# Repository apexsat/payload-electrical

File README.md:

# payload-electrical
PCBs for payload 

## Directory

0_PAY_3D_Model_Library, 0_PAY_Footprint_Library.pretty, 0_PAY_Symbol_Library are libraries for all payload PCBs to use. Use the convention ${KIPRJMOD}/../0_PAY_Symbol_Library/(symbol file) so that library paths are referenced relative to the project path rather than absolute to your specific computer's filesystem.

All PIB and related designs to actually be mounted on satellite should be created as projects in the repo base directory. Any test articles should be created in the test-articles folder. 

simulation should include any relevant MATLAB simulation or spreadsheeting.

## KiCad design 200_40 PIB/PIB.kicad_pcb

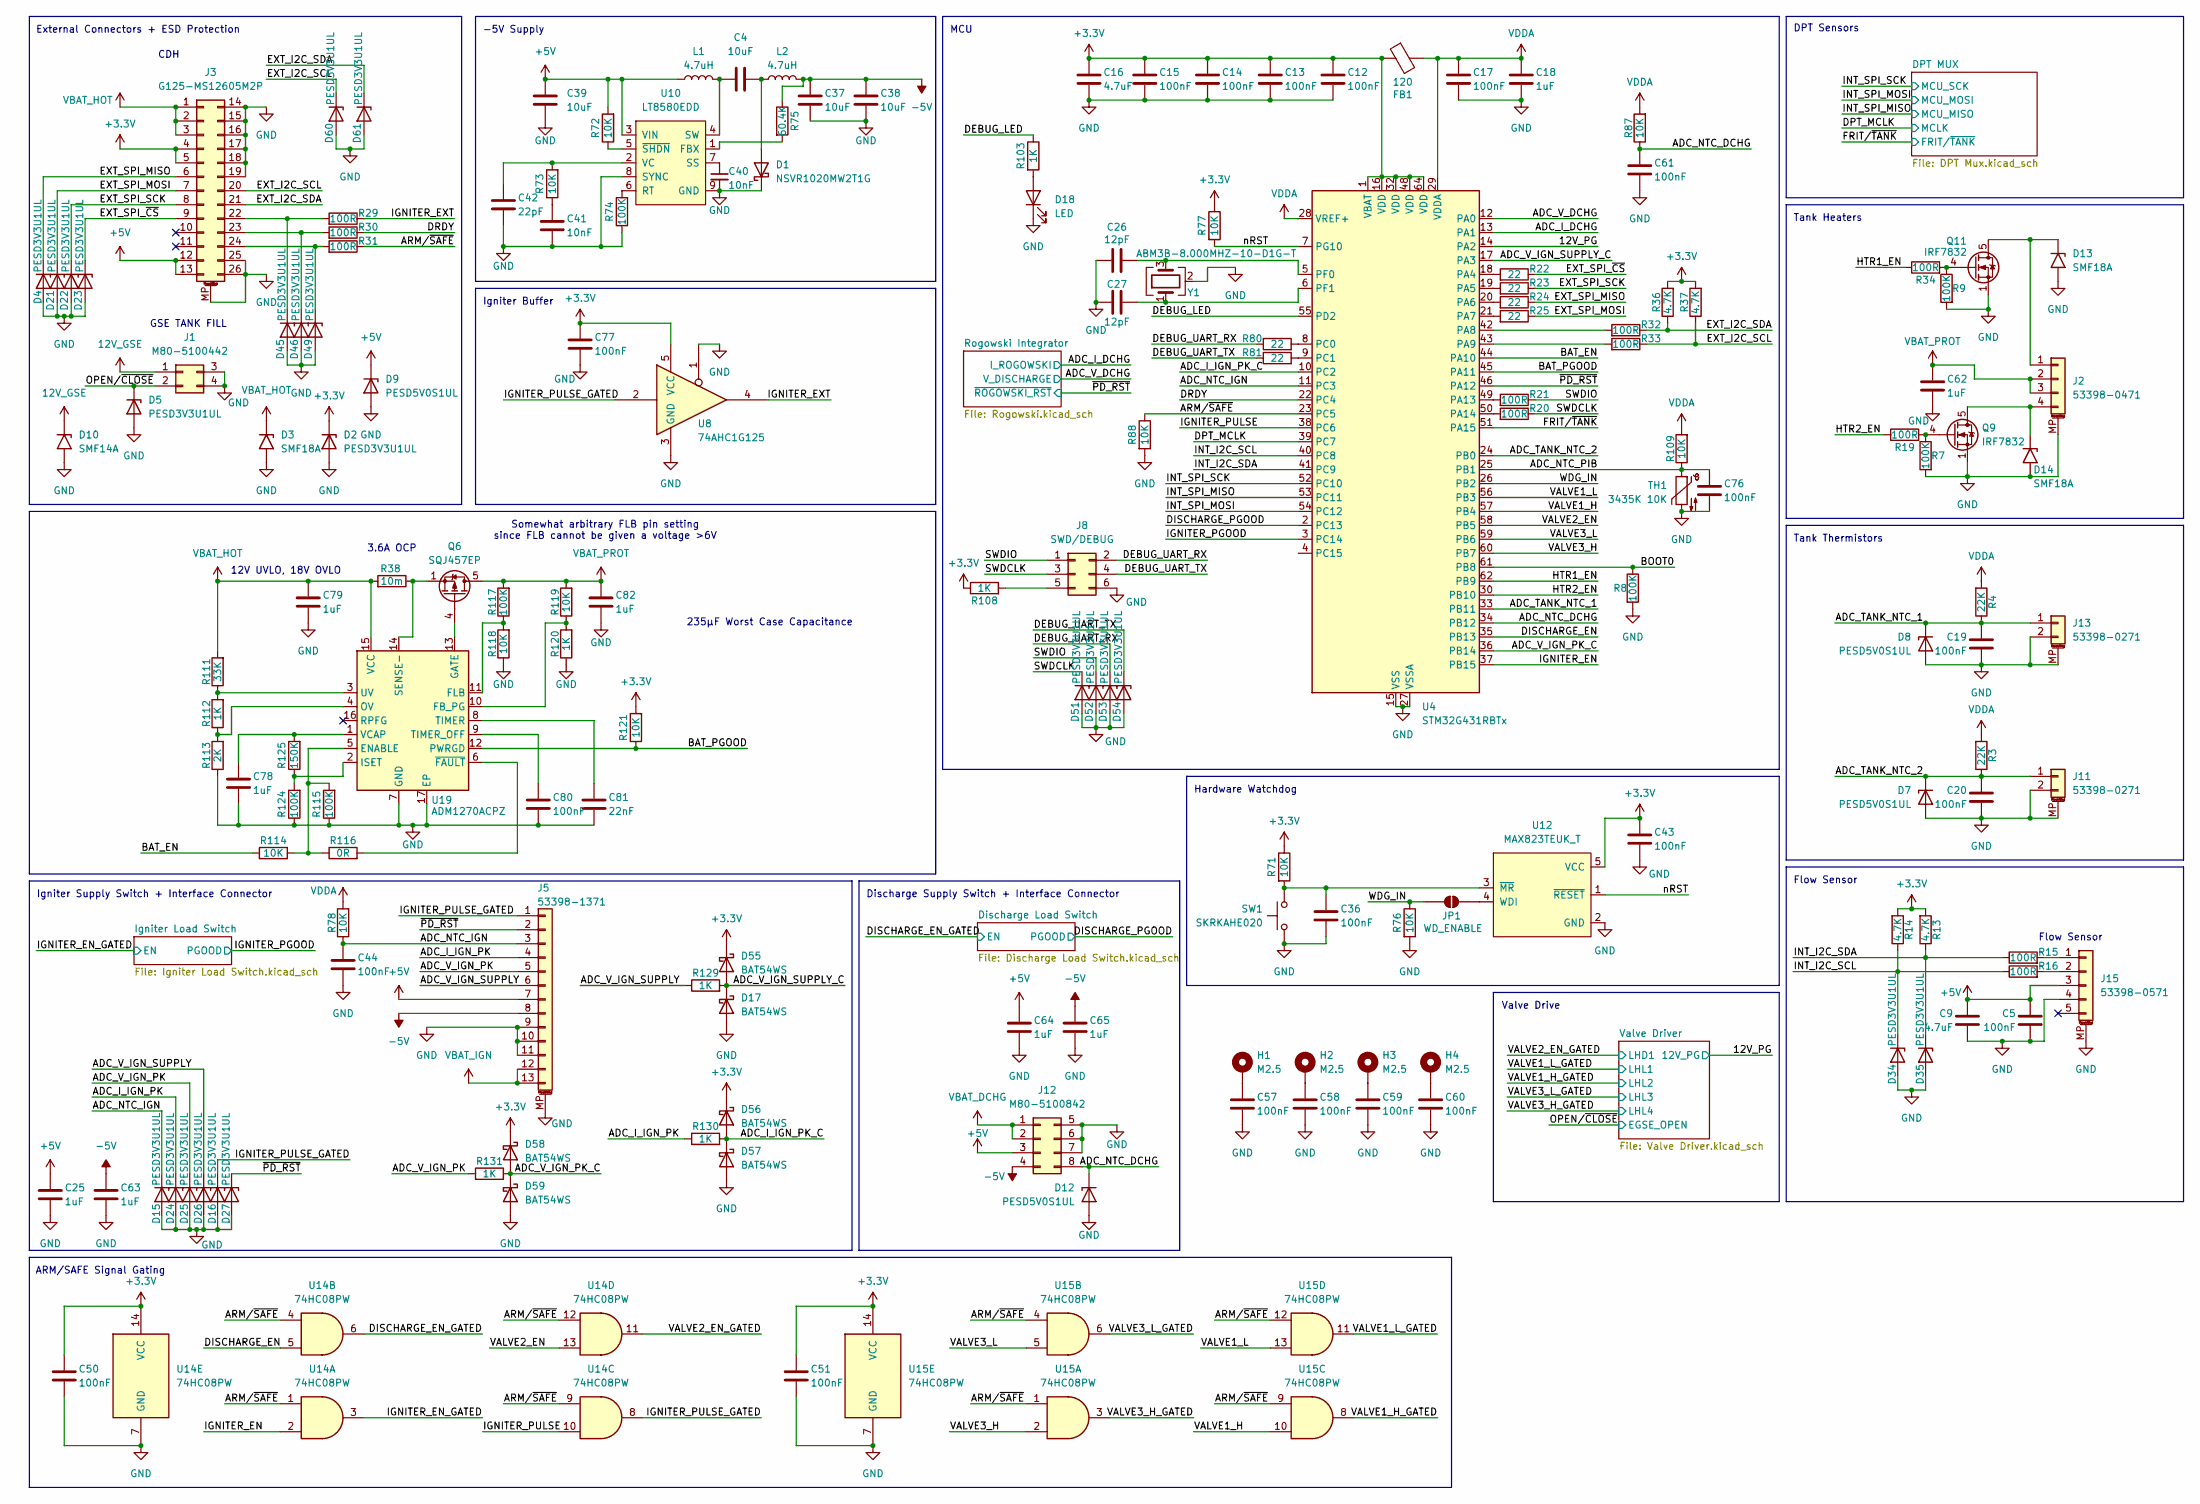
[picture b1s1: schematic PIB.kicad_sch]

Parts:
C4, C37, C38, C39: 10uF; C_0805_2012Metric; Digikey PN 4713-GMC21X7R106K25NTCT-ND
C5, C12, C13, C14, C15, C17, C19, C20, C36, C43, C44, C50, C51, C61, C76, C77, C80: 100nF; C_0402_1005Metric; Digikey PN 490-10672-1-ND
C9, C16: 4.7uF; C_0603_1608Metric; Digikey PN 4713-GMC10X7R475K16NTCT-ND
C18, C25, C62, C63, C64, C65, C78, C79, C82: 1uF; C_0603_1608Metric; Digikey PN 587-3352-1-ND
C26, C27: 12pF; C_0402_1005Metric; Digikey PN 490-16460-1-ND
C40, C41: 10nF; C_0402_1005Metric; Digikey PN 490-4516-1-ND
C42: 22pF; C_0402_1005Metric; Digikey PN 490-16451-1-ND
C57, C58, C59, C60: 100nF; C_0603_1608Metric; Digikey PN 399-C0603C104M5RACTUCT-ND
C81: 22nF; C_0402_1005Metric; Digikey PN 490-4763-1-ND
D1: NSVR1020MW2T1G; D_SOD-323; Digikey PN NSVR1020MW2T1GOSCT-ND
D2, D4, D5, D15, D16, D21, D22, D23, D24, D25, D26, D27, D34, D35, D45, D46, D49, D51, D52, D53, D54, D60, D61: PESD3V3U1UL; D_SOD-882; Digikey PN 1727-4154-1-ND
D3, D13, D14: SMF18A; D_SMF; Digikey PN F5820CT-ND
D7, D8, D9, D12: PESD5V0S1UL; D_SOD-882; Digikey PN 1727-PESD5V0S1ULSYLCT-ND
D10: SMF14A; D_SMF; Digikey PN F5816CT-ND
D17, D55, D56, D57, D58, D59: BAT54WS; D_SOD-323F; Digikey PN 4878-BAT54WSCT-ND
D18: LED; LED_0603_1608Metric; Digikey PN 732-4971-1-ND
FB1: 120; R_0603_1608Metric; Digikey PN 553-2387-1-ND
H1, H2, H3, H4: M2.5; MountingHole_2.7mm_M2.5_DIN965_Pad
J1: M80-5100442; HARWIN_M80-5100442; Digikey PN 952-2343-ND
J2: 53398-0471; Molex_PicoBlade_53398-0471_1x04-1MP_P1.25mm_Vertical; Digikey PN WM7608CT-ND
J3: G125-MS12605M2P; Harwin_Gecko_G125-MS12605M2P_2x13_P1.25mm_Vertical; Digikey PN 952-3677-ND
J5: 53398-1371; Molex_PicoBlade_53398-1371_1x13-1MP_P1.25mm_Vertical; Digikey PN WM7617CT-ND
J8: SWD/DEBUG; PinHeader_2x03_P2.54mm_Vertical_SMD; Digikey PN 952-2121-ND
J11, J13: 53398-0271; Molex_PicoBlade_53398-0271_1x02-1MP_P1.25mm_Vertical; Digikey PN WM7606CT-ND
J12: M80-5100842; HARWIN_M80-5100842; Digikey PN 952-2341-ND
J15: 53398-0571; Molex_PicoBlade_53398-0571_1x05-1MP_P1.25mm_Vertical; Digikey PN WM7609CT-ND
JP1: WD_ENABLE; SolderJumper-2_P1.3mm_Open_Pad1.0x1.5mm
L1, L2: 4.7uH; L_Vishay_IHLP-1616; Digikey PN 541-1051-1-ND
Q6: SQJ457EP; PowerPAK_SO-8_Single; Digikey PN SQJ457EP-T1_GE3CT-ND
Q9, Q11: IRF7832; SOIC-8_3.9x4.9mm_P1.27mm; Digikey PN IRF7832PBFCT-ND
R3, R4: 22K; R_0402_1005Metric; Tolerance 0.1%, 25ppm/C; Digikey PN YAG4210CT-ND
R7, R8, R9, R74, R115, R124: 100K; R_0402_1005Metric; Digikey PN YAG1343CT-ND
R13, R14, R36, R37: 4.7K; R_0402_1005Metric; Digikey PN 311-4.7KLRCT-ND
R15, R16, R19, R20, R21, R29, R30, R31, R32, R33, R34: 100R; R_0402_1005Metric; Digikey PN YAG2301CT-ND
R22, R23, R24, R25, R80, R81: 22; R_0402_1005Metric; Digikey PN 311-22.0LRCT-ND
R38: 10m; R_0805_2012Metric; Digikey PN 273-MCS1320R010FERCT-ND
R71, R72, R73, R76, R77, R88, R114, R121: 10K; R_0402_1005Metric; Digikey PN YAG1346CT-ND
R75: 60.4K; R_0402_1005Metric; Digikey PN YAG1461CT-ND
R78, R87, R109, R118, R119: 10K; R_0402_1005Metric; Tolerance 0.1%, 25ppm/C; Digikey PN YAG1346CT-ND
R103, R108, R129, R130, R131: 1K; R_0402_1005Metric; Digikey PN 13-RT0402BRD131KLCT-ND
R111: 33K; R_0402_1005Metric; Tolerance 0.1%, 25ppm/C; Digikey PN YAG1412CT-ND
R112, R120: 1K; R_0402_1005Metric; Tolerance 0.1%, 25ppm/C; Digikey PN 13-RT0402BRD131KLCT-ND
R113: 2K; R_0402_1005Metric; Tolerance 0.1%, 25ppm/C; Digikey PN YAG2303CT-ND
R116: 0R; R_0402_1005Metric; Digikey PN 311-0.0LRCT-ND
R117: 100K; R_0402_1005Metric; Tolerance 0.1%, 25ppm/C; Digikey PN YAG1343CT-ND
R125: 150K; R_0402_1005Metric; Digikey PN 13-RT0402BRD07150KLCT-ND
SW1: SKRKAHE020; SW_Push_SPST_NO_Alps_SKRK; Digikey PN 4809-SKRKAHE020CT-ND
TH1: 3435K 10K; R_0603_1608Metric; Digikey PN P12011CT-ND
U4: STM32G431RBTx; LQFP-64_10x10mm_P0.5mm; Digikey PN 497-19471-ND
U8: 74AHC1G125; SOT-23-5; Digikey PN 296-8744-1-ND
U10: LT8580EDD; DFN-8_DD; Digikey PN 161-LT8580EDD#TRPBFCT-ND
U12: MAX823TEUK_T; SOT95P280X145-5N; Digikey PN MAX823TEUK+TCT-ND
U14, U15: 74HC08PW; TSSOP-14_4.4x5mm_P0.65mm; Digikey PN 296-26459-5-ND
U19: ADM1270ACPZ; LFCSP-16-1EP_3x3mm_P0.5mm_EP1.5x1.5mm; Digikey PN ADM1270ACPZ-R7CT-ND
Y1: ABM3B-8.000MHZ-10-D1G-T; Crystal_SMD_Abracon_ABM3B-4Pin_5.0x3.2mm; Digikey PN 535-ABM3B-8.000MHZ-10-D1G-TCT-ND

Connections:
12V_GSE: D10.1 (A1), J1.1; also elsewhere on the board
+3.3V: C12.1, C13.1, C14.1, C15.1, C16.1, C43.1, C50.1, C51.1, C77.1, D2.1 (K), D55.1 (K), D56.1 (K), D58.1 (K), FB1.1, J3.4, J3.5, R13.2, R14.2, R36.2, R37.2, R71.1, R77.1, R108.1, R121.2, U4.1 (VBAT), U4.16 (VDD), U4.32 (VDD), U4.48 (VDD), U4.64 (VDD), U8.5 (VCC), U12.5 (VCC), U14.14 (VCC), U15.14 (VCC); also elsewhere on the board
+5V: C5.1, C9.1, C25.1, C39.2, C64.1, D9.1 (K), J3.12, J3.13, J5.7, J12.3, J15.3, L1.1, R72.2, U10.3 (VIN); also elsewhere on the board
-5V: C37.2, C38.2, C63.1, C65.1, J5.8, J12.4, L2.2, R75.1; also elsewhere on the board
/12V_PG: U4.14 (PA2); also elsewhere on the board
/ADC_I_DCHG: U4.13 (PA1); also elsewhere on the board
/ADC_I_IGN_PK: D24.1 (K), J5.4, R130.1
/ADC_I_IGN_PK_C: D56.2 (A), D57.1 (K), R130.2, U4.10 (PC2)
/ADC_NTC_DCHG: C61.1, D12.1 (K), J12.8, R87.1, U4.34 (PB12)
/ADC_NTC_IGN: C44.1, D15.1 (K), J5.3, R78.1, U4.11 (PC3)
/ADC_NTC_PIB: C76.1, R109.1, TH1.1, U4.25 (PB1)
/ADC_TANK_NTC_1: C19.1, D8.1 (K), J13.1, R4.1, U4.33 (PB11)
/ADC_TANK_NTC_2: C20.1, D7.1 (K), J11.1, R3.1, U4.24 (PB0)
/ADC_V_DCHG: U4.12 (PA0); also elsewhere on the board
/ADC_V_IGN_PK: D25.1 (K), J5.5, R131.1
/ADC_V_IGN_PK_C: D58.2 (A), D59.1 (K), R131.2, U4.36 (PB14)
/ADC_V_IGN_SUPPLY: D26.1 (K), J5.6, R129.1
/ADC_V_IGN_SUPPLY_C: D17.1 (K), D55.2 (A), R129.2, U4.17 (PA3)
/ARM/~SAFE: R31.1, R88.1, U4.23 (PC5), U14.1, U14.4, U14.9, U14.12, U15.1, U15.4, U15.9, U15.12
/BAT_EN: R114.1, U4.44 (PA10)
/BAT_PGOOD: R121.1, U4.45 (PA11), U19.12 (PWRGD)
/BOOT0: R8.1, U4.61 (PB8)
/DEBUG_LED: R103.1, U4.55 (PD2)
/DEBUG_UART_RX: D53.1 (K), J8.2, R80.1
/DEBUG_UART_TX: D54.1 (K), J8.4, R81.1
/DISCHARGE_EN: U4.35 (PB13), U14.5
/DISCHARGE_EN_GATED: U14.6; also elsewhere on the board
/DISCHARGE_PGOOD: U4.2 (PC13); also elsewhere on the board
/DPT_MCLK: U4.39 (PC7); also elsewhere on the board
/DRDY: R30.1, U4.22 (PC4)
/EXT_I2C_SCL: D60.1 (K), J3.20, R33.1, R37.1
/EXT_I2C_SDA: D61.1 (K), J3.21, R32.1, R36.1
/EXT_SPI_MISO: D4.1 (K), J3.6, R24.1
/EXT_SPI_MOSI: D21.1 (K), J3.7, R25.1
/EXT_SPI_SCK: D22.1 (K), J3.8, R23.1
/EXT_SPI_~CS: D23.1 (K), J3.9, R22.1
/FRIT/~TANK: U4.51 (PA15); also elsewhere on the board
/HTR1_EN: R34.1, U4.62 (PB9)
/HTR2_EN: R19.1, U4.30 (PB10)
/IGNITER_EN: U4.37 (PB15), U14.2
/IGNITER_EN_GATED: U14.3; also elsewhere on the board
/IGNITER_EXT: R29.1, U8.4
/IGNITER_PGOOD: U4.3 (PC14); also elsewhere on the board
/IGNITER_PULSE: U4.38 (PC6), U14.10
/IGNITER_PULSE_GATED: D16.1 (K), J5.1, U8.2, U14.8
/INT_I2C_SCL: D34.1 (K), R14.1, R16.1, U4.40 (PC8)
/INT_I2C_SDA: D35.1 (K), R13.1, R15.1, U4.41 (PC9)
/INT_SPI_MISO: U4.53 (PC11); also elsewhere on the board
/INT_SPI_MOSI: U4.54 (PC12); also elsewhere on the board
/INT_SPI_SCK: U4.52 (PC10); also elsewhere on the board
/OPEN/~CLOSE: D5.1 (K), J1.2; also elsewhere on the board
/SWDCLK: D51.1 (K), J8.3, R20.1
/SWDIO: D52.1 (K), J8.1, R21.1
/VALVE1_H: U4.57 (PB4), U15.10
/VALVE1_H_GATED: U15.8; also elsewhere on the board
/VALVE1_L: U4.56 (PB3), U15.13
/VALVE1_L_GATED: U15.11; also elsewhere on the board
/VALVE2_EN: U4.58 (PB5), U14.13
/VALVE2_EN_GATED: U14.11; also elsewhere on the board
/VALVE3_H: U4.60 (PB7), U15.2
/VALVE3_H_GATED: U15.3; also elsewhere on the board
/VALVE3_L: U4.59 (PB6), U15.5
/VALVE3_L_GATED: U15.6; also elsewhere on the board
/WDG_IN: JP1.1 (A), R76.1, U4.26 (PB2)
/nRST: R77.2, U4.7 (PG10), U12.1 (~RESET)
/~PD_RST: D27.1 (K), J5.2, U4.46 (PA12); also elsewhere on the board
GND: C5.2, C9.2, C12.2, C13.2, C14.2, C15.2, C16.2, C17.2, C18.2, C19.2, C20.2, C25.2, C26.1, C27.1, C36.2, C37.1, C38.1, C39.1, C40.2, C41.2, C42.2, C43.2, C44.2, C50.2, C51.2, C57.2, C58.2, C59.2, C60.2, C61.2, C62.2, C63.2, C64.2, C65.2, C76.2, C77.2, C78.2, C79.2, C80.2, C81.2, C82.2, D1.1 (K), D2.2 (A), D3.2 (A2), D4.2 (A), D5.2 (A), D7.2 (A), D8.2 (A), D9.2 (A), D10.2 (A2), D12.2 (A), D13.2 (A2), D14.2 (A2), D15.2 (A), D16.2 (A), D17.2 (A), D18.1 (K), D21.2 (A), D22.2 (A), D23.2 (A), D24.2 (A), D25.2 (A), D26.2 (A), D27.2 (A), D34.2 (A), D35.2 (A), D45.2 (A), D46.2 (A), D49.2 (A), D51.2 (A), D52.2 (A), D53.2 (A), D54.2 (A), D57.2 (A), D59.2 (A), D60.2 (A), D61.2 (A), J1.3, J1.4, J2.MP (MountPin), J3.14, J3.15, J3.16, J3.17, J3.18, J3.19, J3.25, J3.26, J3.MP (MountPin), J5.9, J5.10, J5.11, J5.MP (MountPin), J8.6, J11.2, J11.MP (MountPin), J12.5, J12.6, J12.7, J13.2, J13.MP (MountPin), J15.4, J15.MP (MountPin), Q9.1 (S), Q9.2 (S), Q9.3 (S), Q11.1 (S), Q11.2 (S), Q11.3 (S), R7.2, R8.2, R9.2, R74.1, R76.2, R88.2, R113.1, R115.1, R118.1, R120.1, R124.1, SW1.2, TH1.2, U4.15 (VSS), U4.27 (VSSA), U4.31 (VSS), U4.47 (VSS), U4.63 (VSS), U8.1, U8.3 (GND), U10.8 (SYNC), U10.9 (GND), U12.2 (GND), U14.7 (GND), U15.7 (GND), U19.7 (GND), U19.17 (EP), Y1.2 (G), Y1.4 (G); also elsewhere on the board
unnamed: C41.1, R73.1
unnamed: C57.1, H1.1 (1_1)
unnamed: C58.1, H2.1 (1_1)
unnamed: C59.1, H3.1 (1_1)
unnamed: C60.1, H4.1 (1_1)
unnamed: C4.2, D1.2 (A), L2.1
unnamed: D13.1 (A1), J2.1, Q11.5 (D), Q11.6 (D), Q11.7 (D), Q11.8 (D)
unnamed: D14.1 (A1), J2.4, Q9.5 (D), Q9.6 (D), Q9.7 (D), Q9.8 (D)
unnamed: D18.2 (A), R103.2
unnamed: D45.1 (K), J3.22, R29.2
unnamed: D46.1 (K), J3.23, R30.2
unnamed: D49.1 (K), J3.24, R31.2
unnamed: J8.5, R108.2
unnamed: J15.1, R15.2
unnamed: J15.2, R16.2
unnamed: JP1.2 (B), U12.4 (WDI)
unnamed: Q6.4 (G), U19.13 (GATE)
unnamed: Q9.4 (G), R7.1, R19.2
unnamed: Q11.4 (G), R9.1, R34.2
unnamed: R22.2, U4.18 (PA4)
unnamed: R23.2, U4.19 (PA5)
unnamed: R24.2, U4.20 (PA6)
unnamed: R25.2, U4.21 (PA7)
unnamed: R32.2, U4.42 (PA8)
unnamed: R33.2, U4.43 (PA9)
unnamed: R21.2, U4.49 (PA13)
unnamed: R20.2, U4.50 (PA14)
unnamed: R80.2, U4.8 (PC0)
unnamed: R81.2, U4.9 (PC1)
unnamed: C26.2, U4.5 (PF0), Y1.3
unnamed: C27.2, U4.6 (PF1), Y1.1
unnamed: R75.2, U10.1 (FBX)
unnamed: R74.2, U10.6 (RT)
unnamed: C40.1, U10.7 (SS)
unnamed: C4.1, L1.2, U10.4 (SW)
unnamed: C42.1, R73.2, U10.2 (VC)
unnamed: R72.1, U10.5 (~SHDN)
unnamed: C36.1, R71.2, SW1.1, U12.3 (~MR)
unnamed: R114.2, R115.2, R116.1, U19.5 (ENABLE)
unnamed: R119.1, R120.2, U19.10 (FB_PG)
unnamed: R117.1, R118.2, U19.11 (FLB)
unnamed: R124.2, R125.1, U19.2 (ISET)
unnamed: R112.1, R113.2, U19.4 (OV)
unnamed: Q6.1 (S), Q6.2 (S), Q6.3 (S), R38.1, U19.14 (SENSE-)
unnamed: C81.1, U19.8 (TIMER)
unnamed: C80.1, U19.9 (TIMER_OFF)
unnamed: R111.1, R112.2, U19.3 (UV)
unnamed: C78.1, R125.2, U19.1 (VCAP)
unnamed: R116.2, U19.6 (~FAULT)
VBAT_DCHG: J12.1, J12.2; also elsewhere on the board
VBAT_HOT: C79.1, D3.1 (A1), J3.1, J3.2, J3.3, R38.2, R111.2, U19.15 (VCC)
VBAT_IGN: J5.12, J5.13; also elsewhere on the board
VBAT_PROT: C62.1, C82.1, J2.2, J2.3, Q6.5 (D), R117.2, R119.2; also elsewhere on the board
VDDA: C17.1, C18.1, FB1.2, R3.2, R4.2, R78.2, R87.2, R109.2, U4.28 (VREF+), U4.29 (VDDA)

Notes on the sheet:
Tank Thermistors
Flow Sensor
External Connectors + ESD Protection
CDH
Igniter Supply Switch + Interface Connector
-5V Supply
Hardware Watchdog
Somewhat arbitrary FLB pin setting since FLB cannot be given a voltage >6V
ARM/SAFE Signal Gating
Valve Drive
MCU
Discharge Supply Switch + Interface Connector
GSE TANK FILL
3.6A OCP
Tank Heaters
12V UVLO, 18V OVLO
235μF Worst Case Capacitance
Igniter Buffer
DPT Sensors

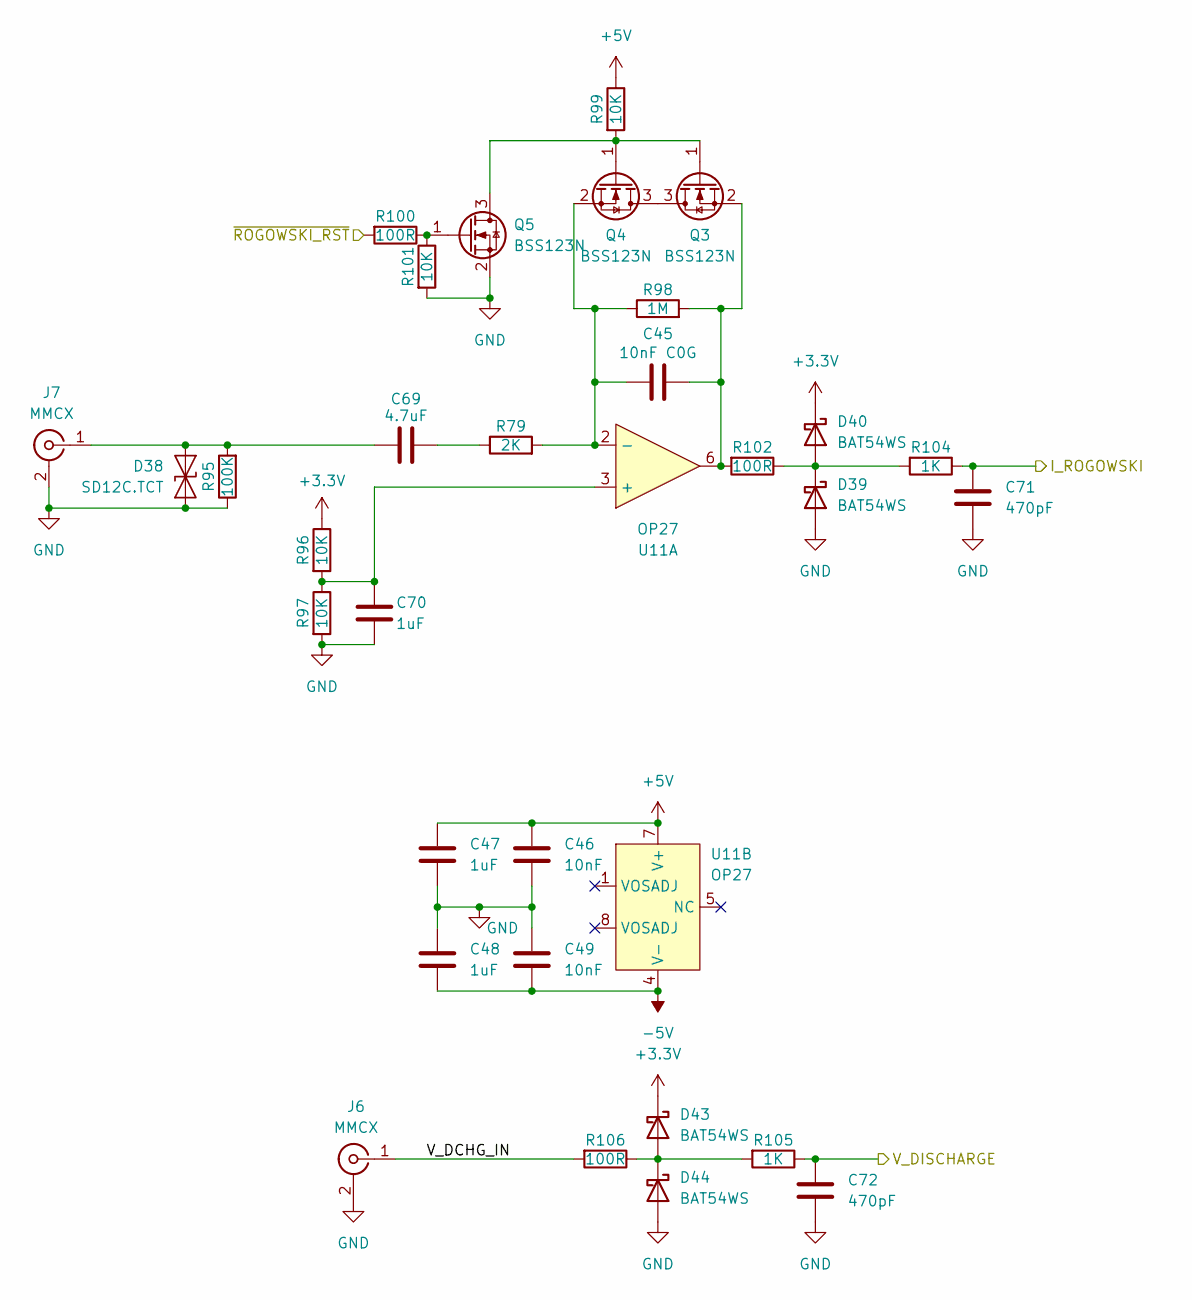
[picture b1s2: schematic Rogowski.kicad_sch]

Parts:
C45: 10nF C0G; C_0603_1608Metric; Digikey PN 490-GRT1885C1E103FA02DCT-ND
C46, C49: 10nF; C_0402_1005Metric; Digikey PN 490-4516-1-ND
C47, C48, C70: 1uF; C_0603_1608Metric; Digikey PN 587-3352-1-ND
C69: 4.7uF; C_0603_1608Metric; Digikey PN 4713-GMC10X7R475K16NTCT-ND
C71, C72: 470pF; C_0402_1005Metric; Digikey PN 490-GCM1555C1H471FA16DCT-ND
D38: SD12C.TCT; D_SOD-323; Digikey PN SD12C.TCTCT-ND
D39, D40, D43, D44: BAT54WS; D_SOD-323F; Digikey PN 4878-BAT54WSCT-ND
J6, J7: MMCX; MMCX_Molex_73415-1471_Vertical; Digikey PN WM5557-ND
Q3, Q4, Q5: BSS123N; SOT-23; Digikey PN BSS123NH6327XTSA1CT-ND
R79: 2K; R_0603_1608Metric; Digikey PN P2.0KDBCT-ND
R95: 100K; R_0603_1608Metric; Digikey PN 2019-RN73R1JTTD1003B25CT-ND
R96, R97, R99, R101: 10K; R_0402_1005Metric; Digikey PN YAG1346CT-ND
R98: 1M; R_0603_1608Metric; Digikey PN 2019-RN73H1JTTD1004B25CT-ND
R100, R102, R106: 100R; R_0402_1005Metric; Digikey PN YAG2301CT-ND
R104, R105: 1K; R_0402_1005Metric; Digikey PN 13-RT0402BRD131KLCT-ND
U11: OP27; SOIC-8_3.9x4.9mm_P1.27mm; Digikey PN 505-OP27GSZ-ND

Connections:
+3.3V: D40.1 (K), D43.1 (K), R96.1; also elsewhere on the board
+5V: C46.1, C47.1, R99.1, U11.7 (V+); also elsewhere on the board
-5V: C48.2, C49.2, U11.4 (V-); also elsewhere on the board
/ADC_I_DCHG: C71.1, R104.1; also elsewhere on the board
/ADC_V_DCHG: C72.1, R105.1; also elsewhere on the board
/Rogowski Integrator/V_DCHG_IN: J6.1 (In), R106.2
/~PD_RST: R100.2; also elsewhere on the board
GND: C46.2, C47.2, C48.1, C49.1, C70.2, C71.2, C72.2, D38.1 (A1), D39.2 (A), D44.2 (A), J6.2 (Ext), J7.2 (Ext), Q5.2 (S), R95.1, R97.2, R101.2; also elsewhere on the board
unnamed: C69.2, R79.1
unnamed: C69.1, D38.2 (A2), J7.1 (In), R95.2
unnamed: D39.1 (K), D40.2 (A), R102.1, R104.2
unnamed: D43.2 (A), D44.1 (K), R105.2, R106.1
unnamed: Q3.3 (D), Q4.3 (D)
unnamed: Q3.1 (G), Q4.1 (G), Q5.3 (D), R99.2
unnamed: C45.2, Q3.2 (S), R98.2, R102.2, U11.6
unnamed: C45.1, Q4.2 (S), R79.2, R98.1, U11.2 (-)
unnamed: Q5.1 (G), R100.1, R101.1
unnamed: C70.1, R96.2, R97.1, U11.3 (+)

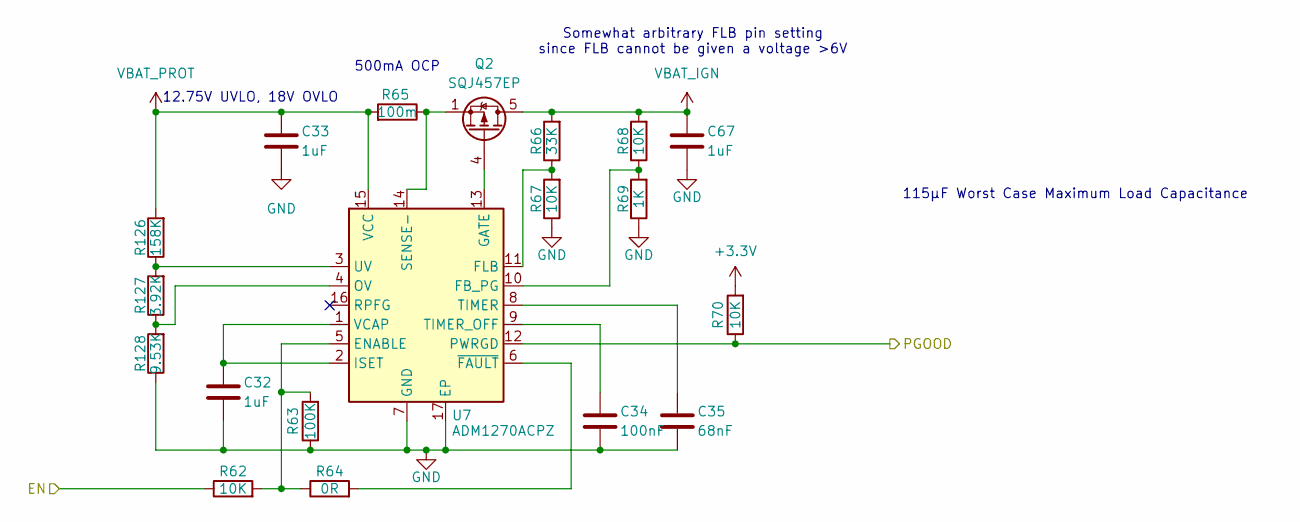
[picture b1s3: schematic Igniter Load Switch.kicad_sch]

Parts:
C32, C33, C67: 1uF; C_0603_1608Metric; Digikey PN 587-3352-1-ND
C34: 100nF; C_0402_1005Metric; Digikey PN 490-10672-1-ND
C35: 68nF; C_0402_1005Metric; Digikey PN 490-14604-1-ND
Q2: SQJ457EP; PowerPAK_SO-8_Single; Digikey PN SQJ457EP-T1_GE3CT-ND
R62, R70: 10K; R_0402_1005Metric; Digikey PN YAG1346CT-ND
R63: 100K; R_0402_1005Metric; Digikey PN YAG1343CT-ND
R64: 0R; R_0402_1005Metric; Digikey PN 311-0.0LRCT-ND
R65: 100m; R_0603_1608Metric; Digikey PN CRL0603-FW-R100ELFCT-ND
R66: 33K; R_0402_1005Metric; Tolerance 0.1%, 25ppm/C; Digikey PN YAG1412CT-ND
R67, R68: 10K; R_0402_1005Metric; Tolerance 0.1%, 25ppm/C; Digikey PN YAG1346CT-ND
R69: 1K; R_0402_1005Metric; Tolerance 0.1%, 25ppm/C; Digikey PN 13-RT0402BRD131KLCT-ND
R126: 158K; R_0402_1005Metric; Tolerance 0.1%, 25ppm/C; Digikey PN A127530CT-ND
R127: 3.92K; R_0402_1005Metric; Tolerance 0.1%, 25ppm/C; Digikey PN YAG1426CT-ND
R128: 9.53K; R_0402_1005Metric; Tolerance 0.1%, 25ppm/C; Digikey PN P9.53KDCCT-ND
U7: ADM1270ACPZ; LFCSP-16-1EP_3x3mm_P0.5mm_EP1.5x1.5mm; Digikey PN ADM1270ACPZ-R7CT-ND

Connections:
+3.3V: R70.2; also elsewhere on the board
/IGNITER_EN_GATED: R62.1; also elsewhere on the board
/IGNITER_PGOOD: R70.1, U7.12 (PWRGD); also elsewhere on the board
GND: C32.2, C33.2, C34.2, C35.2, C67.2, R63.1, R67.1, R69.1, R128.1, U7.7 (GND), U7.17 (EP); also elsewhere on the board
unnamed: Q2.4 (G), U7.13 (GATE)
unnamed: R62.2, R63.2, R64.1, U7.5 (ENABLE)
unnamed: R68.1, R69.2, U7.10 (FB_PG)
unnamed: R66.1, R67.2, U7.11 (FLB)
unnamed: C32.1, U7.1 (VCAP), U7.2 (ISET)
unnamed: R127.1, R128.2, U7.4 (OV)
unnamed: Q2.1 (S), Q2.2 (S), Q2.3 (S), R65.1, U7.14 (SENSE-)
unnamed: C35.1, U7.8 (TIMER)
unnamed: C34.1, U7.9 (TIMER_OFF)
unnamed: R126.1, R127.2, U7.3 (UV)
unnamed: R64.2, U7.6 (~FAULT)
VBAT_IGN: C67.1, Q2.5 (D), R66.2, R68.2; also elsewhere on the board
VBAT_PROT: C33.1, R65.2, R126.2, U7.15 (VCC); also elsewhere on the board

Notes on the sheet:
12.75V UVLO, 18V OVLO
Somewhat arbitrary FLB pin setting since FLB cannot be given a voltage >6V
115μF Worst Case Maximum Load Capacitance
500mA OCP

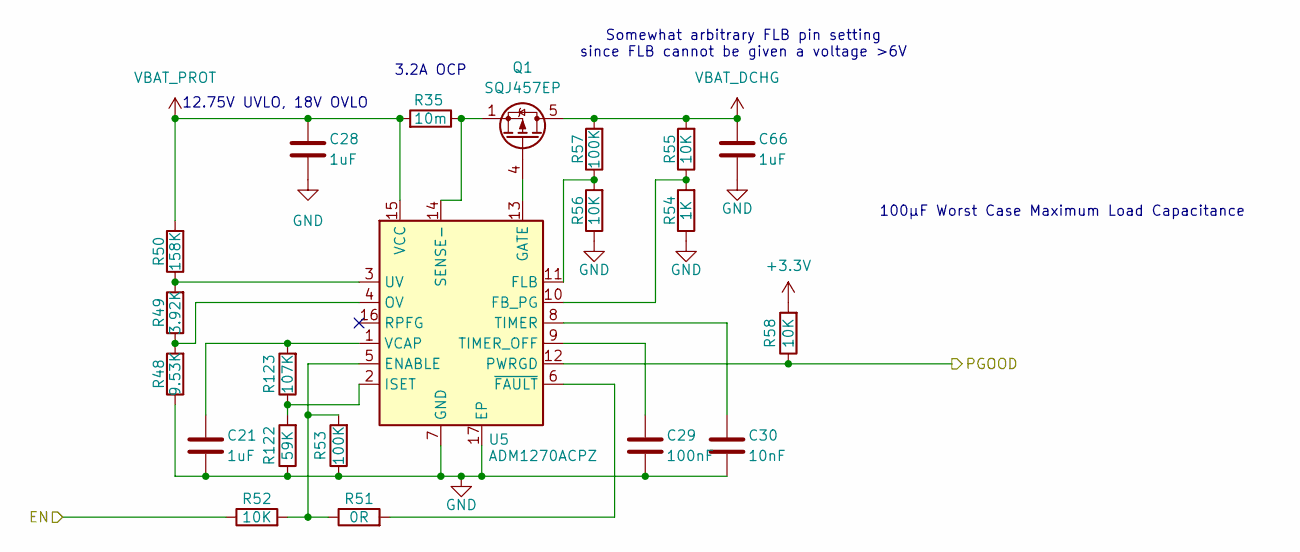
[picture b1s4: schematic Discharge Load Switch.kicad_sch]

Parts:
C21, C28, C66: 1uF; C_0603_1608Metric; Digikey PN 587-3352-1-ND
C29: 100nF; C_0402_1005Metric; Digikey PN 490-10672-1-ND
C30: 10nF; C_0402_1005Metric; Digikey PN 490-4516-1-ND
Q1: SQJ457EP; PowerPAK_SO-8_Single; Digikey PN SQJ457EP-T1_GE3CT-ND
R35: 10m; R_0805_2012Metric; Digikey PN 273-MCS1320R010FERCT-ND
R48: 9.53K; R_0402_1005Metric; Tolerance 0.1%, 25ppm/C; Digikey PN P9.53KDCCT-ND
R49: 3.92K; R_0402_1005Metric; Tolerance 0.1%, 25ppm/C; Digikey PN YAG1426CT-ND
R50: 158K; R_0402_1005Metric; Tolerance 0.1%, 25ppm/C; Digikey PN A127530CT-ND
R51: 0R; R_0402_1005Metric; Digikey PN 311-0.0LRCT-ND
R52, R58: 10K; R_0402_1005Metric; Digikey PN YAG1346CT-ND
R53: 100K; R_0402_1005Metric; Digikey PN YAG1343CT-ND
R54: 1K; R_0402_1005Metric; Tolerance 0.1%, 25ppm/C; Digikey PN 13-RT0402BRD131KLCT-ND
R55, R56: 10K; R_0402_1005Metric; Tolerance 0.1%, 25ppm/C; Digikey PN YAG1346CT-ND
R57: 100K; R_0402_1005Metric; Tolerance 0.1%, 25ppm/C; Digikey PN YAG1343CT-ND
R122: 59K; R_0402_1005Metric; Digikey PN YAG4286CT-ND
R123: 107K; R_0402_1005Metric; Digikey PN 13-RT0402BRD07107KLCT-ND
U5: ADM1270ACPZ; LFCSP-16-1EP_3x3mm_P0.5mm_EP1.5x1.5mm; Digikey PN ADM1270ACPZ-R7CT-ND

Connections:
+3.3V: R58.2; also elsewhere on the board
/DISCHARGE_EN_GATED: R52.1; also elsewhere on the board
/DISCHARGE_PGOOD: R58.1, U5.12 (PWRGD); also elsewhere on the board
GND: C21.2, C28.2, C29.2, C30.2, C66.2, R48.1, R53.1, R54.1, R56.1, R122.1, U5.7 (GND), U5.17 (EP); also elsewhere on the board
unnamed: Q1.4 (G), U5.13 (GATE)
unnamed: R51.1, R52.2, R53.2, U5.5 (ENABLE)
unnamed: R54.2, R55.1, U5.10 (FB_PG)
unnamed: R56.2, R57.1, U5.11 (FLB)
unnamed: R122.2, R123.1, U5.2 (ISET)
unnamed: R48.2, R49.1, U5.4 (OV)
unnamed: Q1.1 (S), Q1.2 (S), Q1.3 (S), R35.1, U5.14 (SENSE-)
unnamed: C30.1, U5.8 (TIMER)
unnamed: C29.1, U5.9 (TIMER_OFF)
unnamed: R49.2, R50.1, U5.3 (UV)
unnamed: C21.1, R123.2, U5.1 (VCAP)
unnamed: R51.2, U5.6 (~FAULT)
VBAT_DCHG: C66.1, Q1.5 (D), R55.2, R57.2; also elsewhere on the board
VBAT_PROT: C28.1, R35.2, R50.2, U5.15 (VCC); also elsewhere on the board

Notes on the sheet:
Somewhat arbitrary FLB pin setting since FLB cannot be given a voltage >6V
12.75V UVLO, 18V OVLO
3.2A OCP
100μF Worst Case Maximum Load Capacitance

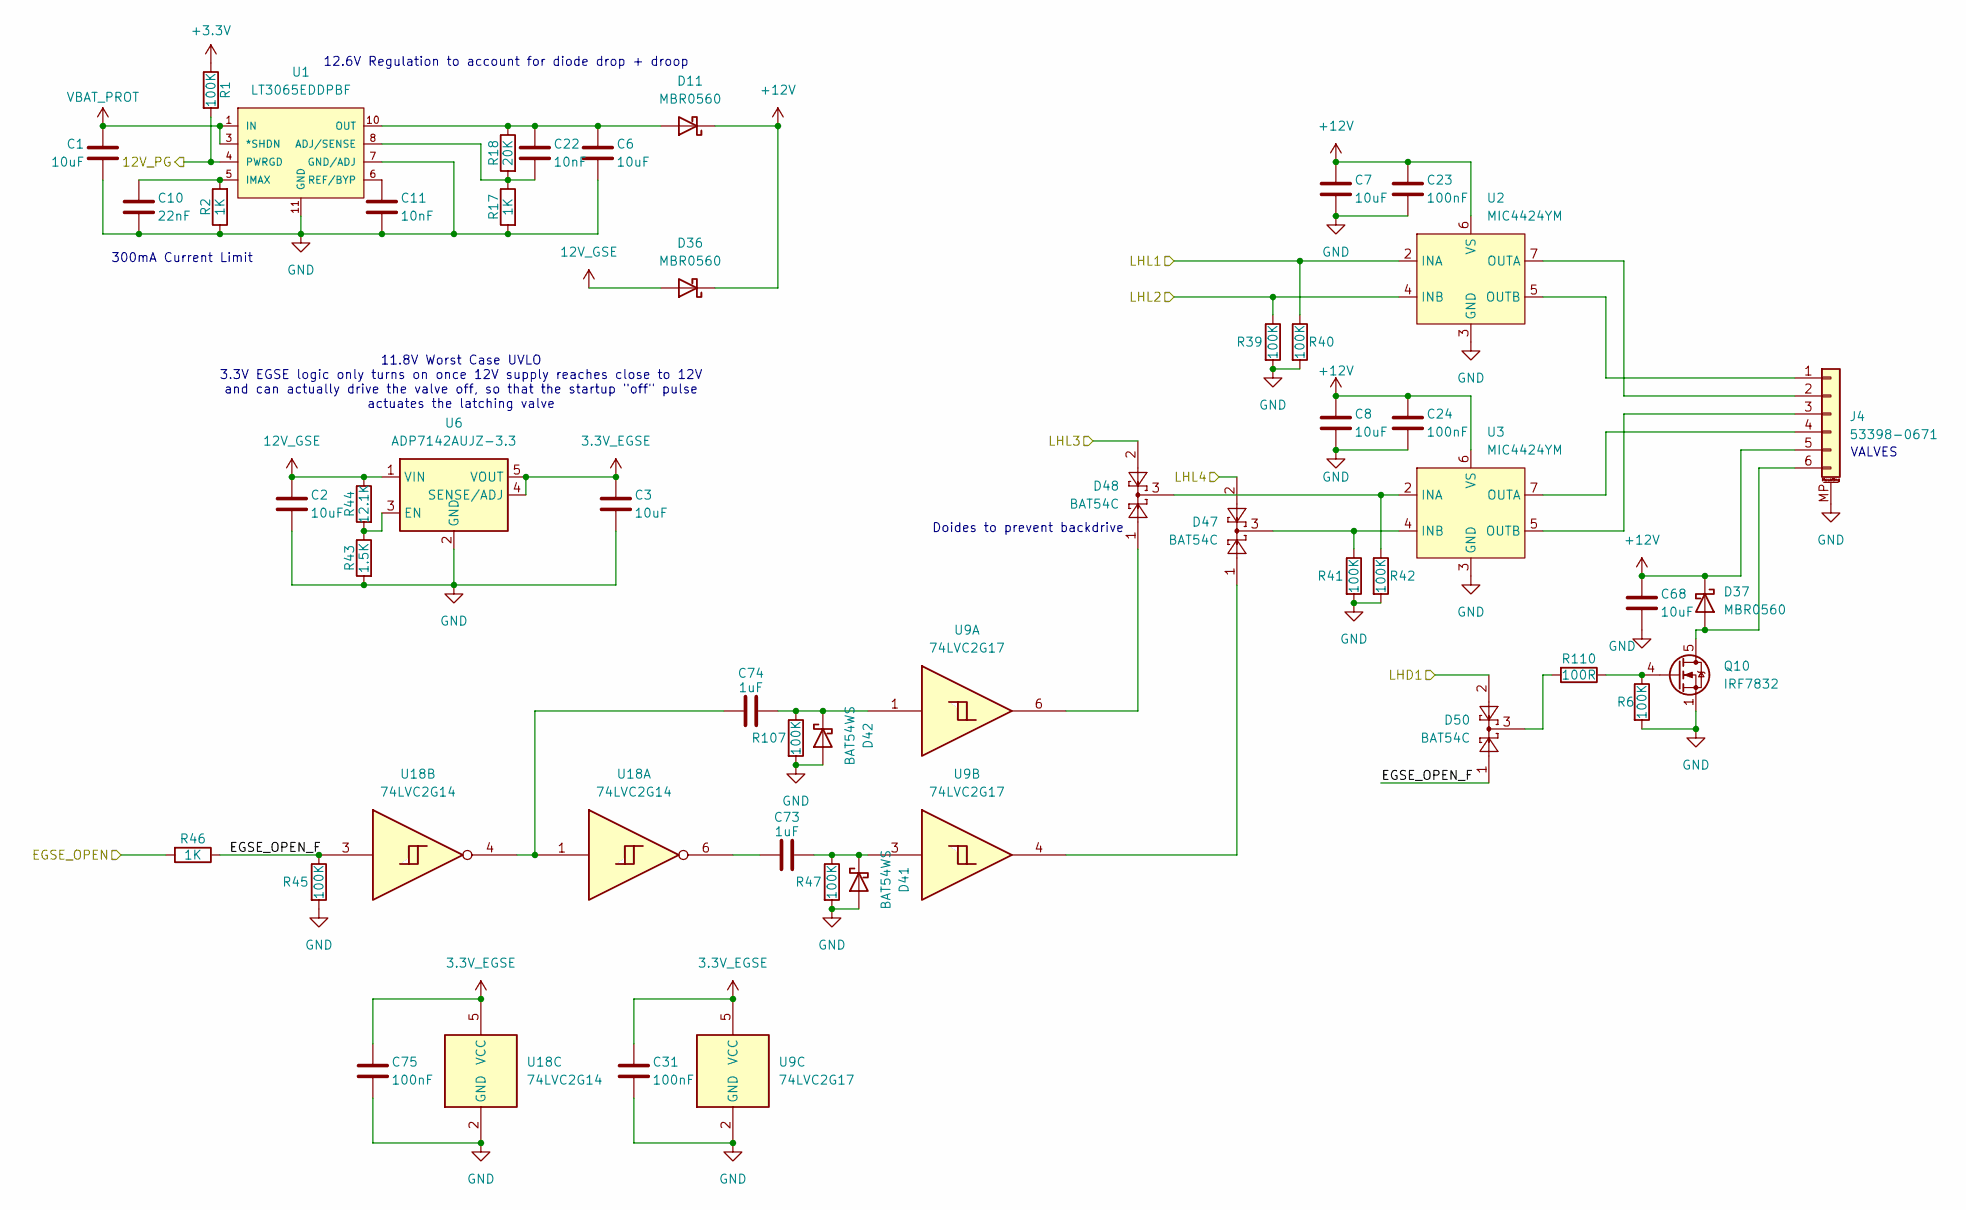
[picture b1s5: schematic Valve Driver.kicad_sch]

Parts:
C1, C2, C3, C6, C7, C8, C68: 10uF; C_0805_2012Metric; Digikey PN 4713-GMC21X7R106K25NTCT-ND
C10: 22nF; C_0402_1005Metric; Digikey PN 490-4763-1-ND
C11, C22: 10nF; C_0402_1005Metric; Digikey PN 490-4516-1-ND
C23, C24, C31, C75: 100nF; C_0402_1005Metric; Digikey PN 490-10672-1-ND
C73, C74: 1uF; C_0402_1005Metric; Digikey PN 490-18216-1-ND
D11, D36, D37: MBR0560; D_SOD-123; Digikey PN 5399-MBR0560CT-ND
D41, D42: BAT54WS; D_SOD-323F; Digikey PN 4878-BAT54WSCT-ND
D47, D48, D50: BAT54C; SOT-23; Digikey PN 4878-BAT54CCT-ND
J4: 53398-0671; Molex_PicoBlade_53398-0671_1x06-1MP_P1.25mm_Vertical; Digikey PN WM7610CT-ND
Q10: IRF7832; SOIC-8_3.9x4.9mm_P1.27mm; Digikey PN IRF7832PBFCT-ND
R1, R6, R39, R40, R41, R42, R45, R47, R107: 100K; R_0402_1005Metric; Digikey PN YAG1343CT-ND
R2, R17, R46: 1K; R_0402_1005Metric; Digikey PN 13-RT0402BRD131KLCT-ND
R18: 20K; R_0402_1005Metric; Digikey PN YAG1388CT-ND
R43: 1.5K; R_0402_1005Metric; Digikey PN 2019-RN73R1ETTP1501B25CT-ND
R44: 12.1K; R_0402_1005Metric; Digikey PN 2019-RN73R1ETTP1212B25CT-ND
R110: 100R; R_0402_1005Metric; Digikey PN YAG2301CT-ND
U1: LT3065EDDPBF; DFN-10_DD; Digikey PN 505-LT3065EDD#PBF-ND
U2, U3: MIC4424YM; SOIC-8_3.9x4.9mm_P1.27mm; Digikey PN 576-1546-1-ND
U6: ADP7142AUJZ-3.3; TSOT-23-5; Digikey PN 505-ADP7142AUJZ-3.3-R7CT-ND
U9: 74LVC2G17; SOT-23-6; Digikey PN 296-SN74LVC2G17DBVRCT-ND
U18: 74LVC2G14; SOT-23-6; Digikey PN 296-26618-1-ND

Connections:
3.3V_EGSE: C3.1, C31.1, C75.1, U6.4 (SENSE/ADJ), U6.5 (VOUT), U9.5 (VCC), U18.5 (VCC)
12V_GSE: C2.1, D36.2 (A), R44.1, U6.1 (VIN); also elsewhere on the board
+3.3V: R1.1; also elsewhere on the board
+12V: C7.1, C8.1, C23.1, C24.1, C68.1, D11.1 (K), D36.1 (K), D37.1 (K), J4.5, U2.6 (VS), U3.6 (VS)
/12V_PG: R1.2, U1.4 (PWRGD); also elsewhere on the board
/OPEN/~CLOSE: R46.2; also elsewhere on the board
/VALVE1_H_GATED: R39.1, U2.4 (INB); also elsewhere on the board
/VALVE1_L_GATED: R40.1, U2.2 (INA); also elsewhere on the board
/VALVE2_EN_GATED: D50.2; also elsewhere on the board
/VALVE3_H_GATED: D47.2; also elsewhere on the board
/VALVE3_L_GATED: D48.2; also elsewhere on the board
/Valve Driver/EGSE_OPEN_F: D50.1, R45.1, R46.1, U18.3
GND: C1.2, C2.2, C3.2, C6.2, C7.2, C8.2, C10.2, C11.2, C23.2, C24.2, C31.2, C68.2, C75.2, D41.2 (A), D42.2 (A), J4.MP (MountPin), Q10.1 (S), Q10.2 (S), Q10.3 (S), R2.1, R6.2, R17.2, R39.2, R40.2, R41.2, R42.2, R43.2, R45.2, R47.2, R107.2, U1.7 (GND/ADJ), U1.11 (GND), U2.3 (GND), U3.3 (GND), U6.2 (GND), U9.2 (GND), U18.2 (GND); also elsewhere on the board
unnamed: C73.1, U18.6
unnamed: C74.1, U18.1, U18.4
unnamed: C6.1, C22.1, D11.2 (A), R18.1, U1.9 (OUT), U1.10 (OUT)
unnamed: D37.2 (A), J4.6, Q10.5 (D), Q10.6 (D), Q10.7 (D), Q10.8 (D)
unnamed: C73.2, D41.1 (K), R47.1, U9.3
unnamed: C74.2, D42.1 (K), R107.1, U9.1
unnamed: D47.1, U9.4
unnamed: D48.1, U9.6
unnamed: D50.3, R110.2
unnamed: J4.1, U2.5 (OUTB)
unnamed: J4.2, U2.7 (OUTA)
unnamed: J4.3, U3.5 (OUTB)
unnamed: J4.4, U3.7 (OUTA)
unnamed: Q10.4 (G), R6.1, R110.1
unnamed: C22.2, R17.1, R18.2, U1.8 (ADJ/SENSE)
unnamed: C10.1, R2.2, U1.5 (IMAX)
unnamed: C11.1, U1.6 (REF/BYP)
unnamed: D48.3, R42.1, U3.2 (INA)
unnamed: D47.3, R41.1, U3.4 (INB)
unnamed: R43.1, R44.2, U6.3 (EN)
VBAT_PROT: C1.1, U1.1 (IN), U1.2 (IN), U1.3 (*SHDN); also elsewhere on the board

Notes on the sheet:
Doides to prevent backdrive
300mA Current Limit
11.8V Worst Case UVLO 3.3V EGSE logic only turns on once 12V supply reaches close to 12V and can actually drive the valve off, so that the startup "off" pulse actuates the latching valve
VALVES
12.6V Regulation to account for diode drop + droop
